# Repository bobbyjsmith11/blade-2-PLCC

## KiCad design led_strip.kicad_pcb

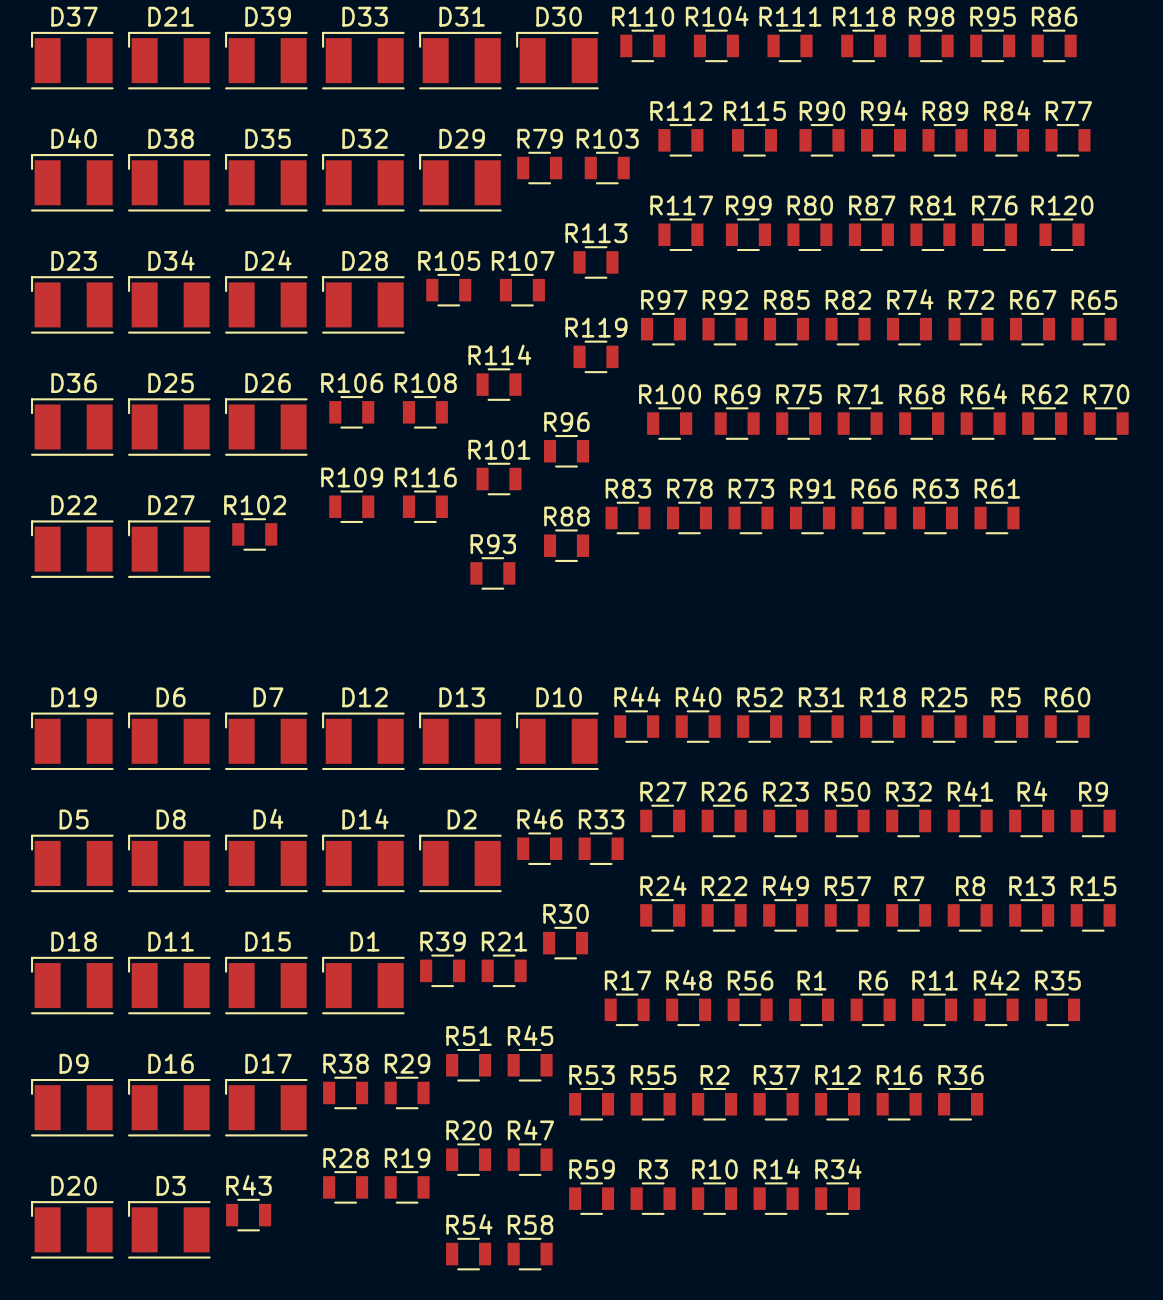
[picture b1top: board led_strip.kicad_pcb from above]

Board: 2 copper layers, 160 parts (0 on the bottom side), 82 nets, no tracks yet.

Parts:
D1, D2, D3, D4, D5, D6, D7, D8, D9, D10, D11, D12, D13, D14, D15, D16, D17, D18, D19, D20, D21, D22, D23, D24, D25, D26, D27, D28, D29, D30, D31, D32, D33, D34, D35, D36, D37, D38, D39, D40: LED; LED_PLCC-2
R1, R4, R7, R10, R13, R16, R19, R22, R25, R28, R31, R34, R37, R40, R43, R46, R49, R52, R55, R58, R61, R64, R67, R70, R73, R76, R79, R82, R85, R88, R91, R94, R97, R100, R103, R106, R109, R112, R115, R118: 287; R_0805
R2, R3, R5, R6, R8, R9, R11, R12, R14, R15, R17, R18, R20, R21, R23, R24, R26, R27, R29, R30, R32, R33, R35, R36, R38, R39, R41, R42, R44, R45, R47, R48, R50, R51, R53, R54, R56, R57, R59, R60, R62, R63, R65, R66, R68, R69, R71, R72, R74, R75, R77, R78, R80, R81, R83, R84, R86, R87, R89, R90, R92, R93, R95, R96, R98, R99, R101, R102, R104, R105, R107, R108, R110, R111, R113, R114, R116, R117, R119, R120: 0; R_0805

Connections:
/Block1/IN: D1.2, R1.2
/Block2/IN: D21.2, R60.1, R61.2
GND: R2.2, R5.2, R8.2, R11.2, R14.2, R17.2, R20.2, R23.2, R26.2, R29.2, R32.2, R35.2, R38.2, R41.2, R44.2, R47.2, R50.2, R53.2, R56.2, R59.2, R62.2, R65.2, R68.2, R71.2, R74.2, R77.2, R80.2, R83.2, R86.2, R89.2, R92.2, R95.2, R98.2, R101.2, R104.2, R107.2, R110.2, R113.2, R116.2, R119.2
unnamed: D1.1, R2.1, R3.2
unnamed: D2.1, R5.1, R6.2
unnamed: D2.2, R3.1, R4.2
unnamed: D3.1, R8.1, R9.2
unnamed: D3.2, R6.1, R7.2
unnamed: D4.1, R11.1, R12.2
unnamed: D4.2, R9.1, R10.2
unnamed: D5.1, R14.1, R15.2
unnamed: D5.2, R12.1, R13.2
unnamed: D6.1, R17.1, R18.2
unnamed: D6.2, R15.1, R16.2
unnamed: D7.1, R20.1, R21.2
unnamed: D7.2, R18.1, R19.2
unnamed: D8.1, R23.1, R24.2
unnamed: D8.2, R21.1, R22.2
unnamed: D9.1, R26.1, R27.2
unnamed: D9.2, R24.1, R25.2
unnamed: D10.1, R29.1, R30.2
unnamed: D10.2, R27.1, R28.2
unnamed: D11.1, R32.1, R33.2
unnamed: D11.2, R30.1, R31.2
unnamed: D12.1, R35.1, R36.2
unnamed: D12.2, R33.1, R34.2
unnamed: D13.1, R38.1, R39.2
unnamed: D13.2, R36.1, R37.2
unnamed: D14.1, R41.1, R42.2
unnamed: D14.2, R39.1, R40.2
unnamed: D15.1, R44.1, R45.2
unnamed: D15.2, R42.1, R43.2
unnamed: D16.1, R47.1, R48.2
unnamed: D16.2, R45.1, R46.2
unnamed: D17.1, R50.1, R51.2
unnamed: D17.2, R48.1, R49.2
unnamed: D18.1, R53.1, R54.2
unnamed: D18.2, R51.1, R52.2
unnamed: D19.1, R56.1, R57.2
unnamed: D19.2, R54.1, R55.2
unnamed: D20.1, R59.1, R60.2
unnamed: D20.2, R57.1, R58.2
unnamed: D21.1, R62.1, R63.2
unnamed: D22.1, R65.1, R66.2
unnamed: D22.2, R63.1, R64.2
unnamed: D23.1, R68.1, R69.2
unnamed: D23.2, R66.1, R67.2
unnamed: D24.1, R71.1, R72.2
unnamed: D24.2, R69.1, R70.2
unnamed: D25.1, R74.1, R75.2
unnamed: D25.2, R72.1, R73.2
unnamed: D26.1, R77.1, R78.2
unnamed: D26.2, R75.1, R76.2
unnamed: D27.1, R80.1, R81.2
unnamed: D27.2, R78.1, R79.2
unnamed: D28.1, R83.1, R84.2
unnamed: D28.2, R81.1, R82.2
unnamed: D29.1, R86.1, R87.2
unnamed: D29.2, R84.1, R85.2
unnamed: D30.1, R89.1, R90.2
unnamed: D30.2, R87.1, R88.2
unnamed: D31.1, R92.1, R93.2
unnamed: D31.2, R90.1, R91.2
unnamed: D32.1, R95.1, R96.2
unnamed: D32.2, R93.1, R94.2
unnamed: D33.1, R98.1, R99.2
unnamed: D33.2, R96.1, R97.2
unnamed: D34.1, R101.1, R102.2
unnamed: D34.2, R99.1, R100.2
unnamed: D35.1, R104.1, R105.2
unnamed: D35.2, R102.1, R103.2
unnamed: D36.1, R107.1, R108.2
unnamed: D36.2, R105.1, R106.2
unnamed: D37.1, R110.1, R111.2
unnamed: D37.2, R108.1, R109.2
unnamed: D38.1, R113.1, R114.2
unnamed: D38.2, R111.1, R112.2
unnamed: D39.1, R116.1, R117.2
unnamed: D39.2, R114.1, R115.2
unnamed: D40.1, R119.1, R120.2
unnamed: D40.2, R117.1, R118.2
VDD: R1.1, R4.1, R7.1, R10.1, R13.1, R16.1, R19.1, R22.1, R25.1, R28.1, R31.1, R34.1, R37.1, R40.1, R43.1, R46.1, R49.1, R52.1, R55.1, R58.1, R61.1, R64.1, R67.1, R70.1, R73.1, R76.1, R79.1, R82.1, R85.1, R88.1, R91.1, R94.1, R97.1, R100.1, R103.1, R106.1, R109.1, R112.1, R115.1, R118.1

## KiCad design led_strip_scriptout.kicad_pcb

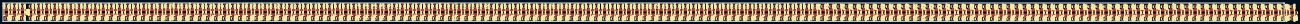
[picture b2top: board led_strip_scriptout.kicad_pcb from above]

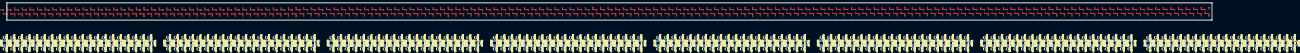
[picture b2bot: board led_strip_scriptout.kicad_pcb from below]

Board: 2 copper layers, 885.2 x 12.7 mm, 1280 parts (640 on the bottom side), 642 nets.

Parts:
D201, D202, D203, D204, D205, D206, D207, D208, D209, D210, D211, D212, D213, D214, D215, D216, D217, D218, D219, D220, D301, D302, D303, D304, D305, D306, D307, D308, D309, D310, D311, D312, D313, D314, D315, D316, D317, D318, D319, D320, D401, D402, D403, D404, D405, D406, D407, D408, D409, D410, D411, D412, D413, D414, D415, D416, D417, D418, D419, D420, D501, D502, D503, D504, D505, D506, D507, D508, D509, D510, D511, D512, D513, D514, D515, D516, D517, D518, D519, D520, D601, D602, D603, D604, D605, D606, D607, D608, D609, D610, D611, D612, D613, D614, D615, D616, D617, D618, D619, D620, D701, D702, D703, D704, D705, D706, D707, D708, D709, D710, D711, D712, D713, D714, D715, D716, D717, D718, D719, D720, D801, D802, D803, D804, D805, D806, D807, D808, D809, D810, D811, D812, D813, D814, D815, D816, D817, D818, D819, D820, D901, D902, D903, D904, D905, D906, D907, D908, D909, D910, D911, D912, D913, D914, D915, D916, D917, D918, D919, D920, D1001, D1002, D1003, D1004, D1005, D1006, D1007, D1008, D1009, D1010, D1011, D1012, D1013, D1014, D1015, D1016, D1017, D1018, D1019, D1020, D1101, D1102, D1103, D1104, D1105, D1106, D1107, D1108, D1109, D1110, D1111, D1112, D1113, D1114, D1115, D1116, D1117, D1118, D1119, D1120, D1201, D1202, D1203, D1204, D1205, D1206, D1207, D1208, D1209, D1210, D1211, D1212, D1213, D1214, D1215, D1216, D1217, D1218, D1219, D1220, D1301, D1302, D1303, D1304, D1305, D1306, D1307, D1308, D1309, D1310, D1311, D1312, D1313, D1314, D1315, D1316, D1317, D1318, D1319, D1320, D1401, D1402, D1403, D1404, D1405, D1406, D1407, D1408, D1409, D1410, D1411, D1412, D1413, D1414, D1415, D1416, D1417, D1418, D1419, D1420, D1501, D1502, D1503, D1504, D1505, D1506, D1507, D1508, D1509, D1510, D1511, D1512, D1513, D1514, D1515, D1516, D1517, D1518, D1519, D1520, D1601, D1602, D1603, D1604, D1605, D1606, D1607, D1608, D1609, D1610, D1611, D1612, D1613, D1614, D1615, D1616, D1617, D1618, D1619, D1620, D1701, D1702, D1703, D1704, D1705, D1706, D1707, D1708, D1709, D1710, D1711, D1712, D1713, D1714, D1715, D1716, D1717, D1718, D1719, D1720: LED; LED_PLCC-2
R201, R204, R207, R210, R213, R216, R219, R222, R225, R228, R231, R234, R237, R240, R243, R246, R249, R252, R255, R258, R301, R304, R307, R310, R313, R316, R319, R322, R325, R328, R331, R334, R337, R340, R343, R346, R349, R352, R355, R358, R401, R404, R407, R410, R413, R416, R419, R422, R425, R428, R431, R434, R437, R440, R443, R446, R449, R452, R455, R458, R501, R504, R507, R510, R513, R516, R519, R522, R525, R528, R531, R534, R537, R540, R543, R546, R549, R552, R555, R558, R601, R604, R607, R610, R613, R616, R619, R622, R625, R628, R631, R634, R637, R640, R643, R646, R649, R652, R655, R658, R701, R704, R707, R710, R713, R716, R719, R722, R725, R728, R731, R734, R737, R740, R743, R746, R749, R752, R755, R758, R801, R804, R807, R810, R813, R816, R819, R822, R825, R828, R831, R834, R837, R840, R843, R846, R849, R852, R855, R858, R901, R904, R907, R910, R913, R916, R919, R922, R925, R928, R931, R934, R937, R940, R943, R946, R949, R952, R955, R958, R1001, R1004, R1007, R1010, R1013, R1016, R1019, R1022, R1025, R1028, R1031, R1034, R1037, R1040, R1043, R1046, R1049, R1052, R1055, R1058, R1101, R1104, R1107, R1110, R1113, R1116, R1119, R1122, R1125, R1128, R1131, R1134, R1137, R1140, R1143, R1146, R1149, R1152, R1155, R1158, R1201, R1204, R1207, R1210, R1213, R1216, R1219, R1222, R1225, R1228, R1231, R1234, R1237, R1240, R1243, R1246, R1249, R1252, R1255, R1258, R1301, R1304, R1307, R1310, R1313, R1316, R1319, R1322, R1325, R1328, R1331, R1334, R1337, R1340, R1343, R1346, R1349, R1352, R1355, R1358, R1401, R1404, R1407, R1410, R1413, R1416, R1419, R1422, R1425, R1428, R1431, R1434, R1437, R1440, R1443, R1446, R1449, R1452, R1455, R1458, R1501, R1504, R1507, R1510, R1513, R1516, R1519, R1522, R1525, R1528, R1531, R1534, R1537, R1540, R1543, R1546, R1549, R1552, R1555, R1558, R1601, R1604, R1607, R1610, R1613, R1616, R1619, R1622, R1625, R1628, R1631, R1634, R1637, R1640, R1643, R1646, R1649, R1652, R1655, R1658, R1701, R1704, R1707, R1710, R1713, R1716, R1719, R1722, R1725, R1728, R1731, R1734, R1737, R1740, R1743, R1746, R1749, R1752, R1755, R1758: 287; R_0805
R202, R203, R205, R206, R208, R209, R211, R212, R214, R215, R217, R218, R220, R221, R223, R224, R226, R227, R229, R230, R232, R233, R235, R236, R238, R239, R241, R242, R244, R245, R247, R248, R250, R251, R253, R254, R256, R257, R259, R260, R302, R303, R305, R306, R308, R309, R311, R312, R314, R315, R317, R318, R320, R321, R323, R324, R326, R327, R329, R330, R332, R333, R335, R336, R338, R339, R341, R342, R344, R345, R347, R348, R350, R351, R353, R354, R356, R357, R359, R360, R402, R403, R405, R406, R408, R409, R411, R412, R414, R415, R417, R418, R420, R421, R423, R424, R426, R427, R429, R430, R432, R433, R435, R436, R438, R439, R441, R442, R444, R445, R447, R448, R450, R451, R453, R454, R456, R457, R459, R460, R502, R503, R505, R506, R508, R509, R511, R512, R514, R515, R517, R518, R520, R521, R523, R524, R526, R527, R529, R530, R532, R533, R535, R536, R538, R539, R541, R542, R544, R545, R547, R548, R550, R551, R553, R554, R556, R557, R559, R560, R602, R603, R605, R606, R608, R609, R611, R612, R614, R615, R617, R618, R620, R621, R623, R624, R626, R627, R629, R630, R632, R633, R635, R636, R638, R639, R641, R642, R644, R645, R647, R648, R650, R651, R653, R654, R656, R657, R659, R660, R702, R703, R705, R706, R708, R709, R711, R712, R714, R715, R717, R718, R720, R721, R723, R724, R726, R727, R729, R730, R732, R733, R735, R736, R738, R739, R741, R742, R744, R745, R747, R748, R750, R751, R753, R754, R756, R757, R759, R760, R802, R803, R805, R806, R808, R809, R811, R812, R814, R815, R817, R818, R820, R821, R823, R824, R826, R827, R829, R830, R832, R833, R835, R836, R838, R839, R841, R842, R844, R845, R847, R848, R850, R851, R853, R854, R856, R857, R859, R860, R902, R903, R905, R906, R908, R909, R911, R912, R914, R915, R917, R918, R920, R921, R923, R924, R926, R927, R929, R930, R932, R933, R935, R936, R938, R939, R941, R942, R944, R945, R947, R948, R950, R951, R953, R954, R956, R957, R959, R960, R1002, R1003, R1005, R1006, R1008, R1009, R1011, R1012, R1014, R1015, R1017, R1018, R1020, R1021, R1023, R1024, R1026, R1027, R1029, R1030, R1032, R1033, R1035, R1036, R1038, R1039, R1041, R1042, R1044, R1045, R1047, R1048, R1050, R1051, R1053, R1054, R1056, R1057, R1059, R1060, R1102, R1103, R1105, R1106, R1108, R1109, R1111, R1112, R1114, R1115, R1117, R1118, R1120, R1121, R1123, R1124, R1126, R1127, R1129, R1130, R1132, R1133, R1135, R1136, R1138, R1139, R1141, R1142, R1144, R1145, R1147, R1148, R1150, R1151, R1153, R1154, R1156, R1157, R1159, R1160, R1202, R1203, R1205, R1206, R1208, R1209, R1211, R1212, R1214, R1215, R1217, R1218, R1220, R1221, R1223, R1224, R1226, R1227, R1229, R1230, R1232, R1233, R1235, R1236, R1238, R1239, R1241, R1242, R1244, R1245, R1247, R1248, R1250, R1251, R1253, R1254, R1256, R1257, R1259, R1260, R1302, R1303, R1305, R1306, R1308, R1309, R1311, R1312, R1314, R1315, R1317, R1318, R1320, R1321, R1323, R1324, R1326, R1327, R1329, R1330, R1332, R1333, R1335, R1336, R1338, R1339, R1341, R1342, R1344, R1345, R1347, R1348, R1350, R1351, R1353, R1354, R1356, R1357, R1359, R1360, R1402, R1403, R1405, R1406, R1408, R1409, R1411, R1412, R1414, R1415, R1417, R1418, R1420, R1421, R1423, R1424, R1426, R1427, R1429, R1430, R1432, R1433, R1435, R1436, R1438, R1439, R1441, R1442, R1444, R1445, R1447, R1448, R1450, R1451, R1453, R1454, R1456, R1457, R1459, R1460, R1502, R1503, R1505, R1506, R1508, R1509, R1511, R1512, R1514, R1515, R1517, R1518, R1520, R1521, R1523, R1524, R1526, R1527, R1529, R1530, R1532, R1533, R1535, R1536, R1538, R1539, R1541, R1542, R1544, R1545, R1547, R1548, R1550, R1551, R1553, R1554, R1556, R1557, R1559, R1560, R1602, R1603, R1605, R1606, R1608, R1609, R1611, R1612, R1614, R1615, R1617, R1618, R1620, R1621, R1623, R1624, R1626, R1627, R1629, R1630, R1632, R1633, R1635, R1636, R1638, R1639, R1641, R1642, R1644, R1645, R1647, R1648, R1650, R1651, R1653, R1654, R1656, R1657, R1659, R1660, R1702, R1703, R1705, R1706, R1708, R1709, R1711, R1712, R1714, R1715, R1717, R1718, R1720, R1721, R1723, R1724, R1726, R1727, R1729, R1730, R1732, R1733, R1735, R1736, R1738, R1739, R1741, R1742, R1744, R1745, R1747, R1748, R1750, R1751, R1753, R1754, R1756, R1757, R1759, R1760: 0; R_0805

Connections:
/Block1/IN: D201.2, R201.2
/Block2/IN: D301.2, R260.1, R301.2
/Block3/IN: D401.2, R360.1, R401.2
/Block4/IN: D501.2, R460.1, R501.2
/Block5/IN: D601.2, R560.1, R601.2
/Block6/IN: D701.2, R660.1, R701.2
/Block7/IN: D801.2, R760.1, R801.2
/Block8/IN: D901.2, R860.1, R901.2
/Block9/IN: D1001.2, R1001.2
/Block10/IN: D1101.2, R1060.1, R1101.2
/Block11/IN: D1201.2, R1160.1, R1201.2
/Block12/IN: D1301.2, R1260.1, R1301.2
/Block13/IN: D1401.2, R1360.1, R1401.2
/Block14/IN: D1501.2, R1460.1, R1501.2
/Block15/IN: D1601.2, R1560.1, R1601.2
/Block16/IN: D1701.2, R1660.1, R1701.2
GND: R202.2, R205.2, R208.2, R211.2, R214.2, R217.2, R220.2, R223.2, R226.2, R229.2, R232.2, R235.2, R238.2, R241.2, R244.2, R247.2, R250.2, R253.2, R256.2, R259.2, R302.2, R305.2, R308.2, R311.2, R314.2, R317.2, R320.2, R323.2, R326.2, R329.2, R332.2, R335.2, R338.2, R341.2, R344.2, R347.2, R350.2, R353.2, R356.2, R359.2, R402.2, R405.2, R408.2, R411.2, R414.2, R417.2, R420.2, R423.2, R426.2, R429.2, R432.2, R435.2, R438.2, R441.2, R444.2, R447.2, R450.2, R453.2, R456.2, R459.2, R502.2, R505.2, R508.2, R511.2, R514.2, R517.2, R520.2, R523.2, R526.2, R529.2, R532.2, R535.2, R538.2, R541.2, R544.2, R547.2, R550.2, R553.2, R556.2, R559.2, R602.2, R605.2, R608.2, R611.2, R614.2, R617.2, R620.2, R623.2, R626.2, R629.2, R632.2, R635.2, R638.2, R641.2, R644.2, R647.2, R650.2, R653.2, R656.2, R659.2, R702.2, R705.2, R708.2, R711.2, R714.2, R717.2, R720.2, R723.2, R726.2, R729.2, R732.2, R735.2, R738.2, R741.2, R744.2, R747.2, R750.2, R753.2, R756.2, R759.2, R802.2, R805.2, R808.2, R811.2, R814.2, R817.2, R820.2, R823.2, R826.2, R829.2, R832.2, R835.2, R838.2, R841.2, R844.2, R847.2, R850.2, R853.2, R856.2, R859.2, R902.2, R905.2, R908.2, R911.2, R914.2, R917.2, R920.2, R923.2, R926.2, R929.2, R932.2, R935.2, R938.2, R941.2, R944.2, R947.2, R950.2, R953.2, R956.2, R959.2, R1002.2, R1005.2, R1008.2, R1011.2, R1014.2, R1017.2, R1020.2, R1023.2, R1026.2, R1029.2, R1032.2, R1035.2, R1038.2, R1041.2, R1044.2, R1047.2, R1050.2, R1053.2, R1056.2, R1059.2, R1102.2, R1105.2, R1108.2, R1111.2, R1114.2, R1117.2, R1120.2, R1123.2, R1126.2, R1129.2, R1132.2, R1135.2, R1138.2, R1141.2, R1144.2, R1147.2, R1150.2, R1153.2, R1156.2, R1159.2, R1202.2, R1205.2, R1208.2, R1211.2, R1214.2, R1217.2, R1220.2, R1223.2, R1226.2, R1229.2, R1232.2, R1235.2, R1238.2, R1241.2, R1244.2, R1247.2, R1250.2, R1253.2, R1256.2, R1259.2, R1302.2, R1305.2, R1308.2, R1311.2, R1314.2, R1317.2, R1320.2, R1323.2, R1326.2, R1329.2, R1332.2, R1335.2, R1338.2, R1341.2, R1344.2, R1347.2, R1350.2, R1353.2, R1356.2, R1359.2, R1402.2, R1405.2, R1408.2, R1411.2, R1414.2, R1417.2, R1420.2, R1423.2, R1426.2, R1429.2, R1432.2, R1435.2, R1438.2, R1441.2, R1444.2, R1447.2, R1450.2, R1453.2, R1456.2, R1459.2, R1502.2, R1505.2, R1508.2, R1511.2, R1514.2, R1517.2, R1520.2, R1523.2, R1526.2, R1529.2, R1532.2, R1535.2, R1538.2, R1541.2, R1544.2, R1547.2, R1550.2, R1553.2, R1556.2, R1559.2, R1602.2, R1605.2, R1608.2, R1611.2, R1614.2, R1617.2, R1620.2, R1623.2, R1626.2, R1629.2, R1632.2, R1635.2, R1638.2, R1641.2, R1644.2, R1647.2, R1650.2, R1653.2, R1656.2, R1659.2, R1702.2, R1705.2, R1708.2, R1711.2, R1714.2, R1717.2, R1720.2, R1723.2, R1726.2, R1729.2, R1732.2, R1735.2, R1738.2, R1741.2, R1744.2, R1747.2, R1750.2, R1753.2, R1756.2, R1759.2
unnamed: D201.1, R202.1, R203.2
unnamed: D202.1, R205.1, R206.2
unnamed: D202.2, R203.1, R204.2
unnamed: D203.1, R208.1, R209.2
unnamed: D203.2, R206.1, R207.2
unnamed: D204.1, R211.1, R212.2
unnamed: D204.2, R209.1, R210.2
unnamed: D205.1, R214.1, R215.2
unnamed: D205.2, R212.1, R213.2
unnamed: D206.1, R217.1, R218.2
unnamed: D206.2, R215.1, R216.2
unnamed: D207.1, R220.1, R221.2
unnamed: D207.2, R218.1, R219.2
unnamed: D208.1, R223.1, R224.2
unnamed: D208.2, R221.1, R222.2
unnamed: D209.1, R226.1, R227.2
unnamed: D209.2, R224.1, R225.2
unnamed: D210.1, R229.1, R230.2
unnamed: D210.2, R227.1, R228.2
unnamed: D211.1, R232.1, R233.2
unnamed: D211.2, R230.1, R231.2
unnamed: D212.1, R235.1, R236.2
unnamed: D212.2, R233.1, R234.2
unnamed: D213.1, R238.1, R239.2
unnamed: D213.2, R236.1, R237.2
unnamed: D214.1, R241.1, R242.2
unnamed: D214.2, R239.1, R240.2
unnamed: D215.1, R244.1, R245.2
unnamed: D215.2, R242.1, R243.2
unnamed: D216.1, R247.1, R248.2
unnamed: D216.2, R245.1, R246.2
unnamed: D217.1, R250.1, R251.2
unnamed: D217.2, R248.1, R249.2
unnamed: D218.1, R253.1, R254.2
unnamed: D218.2, R251.1, R252.2
unnamed: D219.1, R256.1, R257.2
unnamed: D219.2, R254.1, R255.2
unnamed: D220.1, R259.1, R260.2
unnamed: D220.2, R257.1, R258.2
unnamed: D301.1, R302.1, R303.2
unnamed: D302.1, R305.1, R306.2
unnamed: D302.2, R303.1, R304.2
unnamed: D303.1, R308.1, R309.2
unnamed: D303.2, R306.1, R307.2
unnamed: D304.1, R311.1, R312.2
unnamed: D304.2, R309.1, R310.2
unnamed: D305.1, R314.1, R315.2
unnamed: D305.2, R312.1, R313.2
unnamed: D306.1, R317.1, R318.2
unnamed: D306.2, R315.1, R316.2
unnamed: D307.1, R320.1, R321.2
unnamed: D307.2, R318.1, R319.2
unnamed: D308.1, R323.1, R324.2
unnamed: D308.2, R321.1, R322.2
unnamed: D309.1, R326.1, R327.2
unnamed: D309.2, R324.1, R325.2
unnamed: D310.1, R329.1, R330.2
unnamed: D310.2, R327.1, R328.2
unnamed: D311.1, R332.1, R333.2
unnamed: D311.2, R330.1, R331.2
unnamed: D312.1, R335.1, R336.2
unnamed: D312.2, R333.1, R334.2
unnamed: D313.1, R338.1, R339.2
unnamed: D313.2, R336.1, R337.2
unnamed: D314.1, R341.1, R342.2
unnamed: D314.2, R339.1, R340.2
unnamed: D315.1, R344.1, R345.2
unnamed: D315.2, R342.1, R343.2
unnamed: D316.1, R347.1, R348.2
unnamed: D316.2, R345.1, R346.2
unnamed: D317.1, R350.1, R351.2
unnamed: D317.2, R348.1, R349.2
unnamed: D318.1, R353.1, R354.2
unnamed: D318.2, R351.1, R352.2
unnamed: D319.1, R356.1, R357.2
unnamed: D319.2, R354.1, R355.2
unnamed: D320.1, R359.1, R360.2
unnamed: D320.2, R357.1, R358.2
unnamed: D401.1, R402.1, R403.2
unnamed: D402.1, R405.1, R406.2
unnamed: D402.2, R403.1, R404.2
unnamed: D403.1, R408.1, R409.2
unnamed: D403.2, R406.1, R407.2
unnamed: D404.1, R411.1, R412.2
unnamed: D404.2, R409.1, R410.2
unnamed: D405.1, R414.1, R415.2
unnamed: D405.2, R412.1, R413.2
unnamed: D406.1, R417.1, R418.2
unnamed: D406.2, R415.1, R416.2
unnamed: D407.1, R420.1, R421.2
unnamed: D407.2, R418.1, R419.2
unnamed: D408.1, R423.1, R424.2
unnamed: D408.2, R421.1, R422.2
unnamed: D409.1, R426.1, R427.2
unnamed: D409.2, R424.1, R425.2
unnamed: D410.1, R429.1, R430.2
unnamed: D410.2, R427.1, R428.2
unnamed: D411.1, R432.1, R433.2
unnamed: D411.2, R430.1, R431.2
unnamed: D412.1, R435.1, R436.2
unnamed: D412.2, R433.1, R434.2
unnamed: D413.1, R438.1, R439.2
unnamed: D413.2, R436.1, R437.2
unnamed: D414.1, R441.1, R442.2
unnamed: D414.2, R439.1, R440.2
unnamed: D415.1, R444.1, R445.2
unnamed: D415.2, R442.1, R443.2
unnamed: D416.1, R447.1, R448.2
unnamed: D416.2, R445.1, R446.2
unnamed: D417.1, R450.1, R451.2
unnamed: D417.2, R448.1, R449.2
unnamed: D418.1, R453.1, R454.2
unnamed: D418.2, R451.1, R452.2
unnamed: D419.1, R456.1, R457.2
unnamed: D419.2, R454.1, R455.2
unnamed: D420.1, R459.1, R460.2
unnamed: D420.2, R457.1, R458.2
unnamed: D501.1, R502.1, R503.2
unnamed: D502.1, R505.1, R506.2
unnamed: D502.2, R503.1, R504.2
unnamed: D503.1, R508.1, R509.2
unnamed: D503.2, R506.1, R507.2
unnamed: D504.1, R511.1, R512.2
unnamed: D504.2, R509.1, R510.2
unnamed: D505.1, R514.1, R515.2
unnamed: D505.2, R512.1, R513.2
unnamed: D506.1, R517.1, R518.2
unnamed: D506.2, R515.1, R516.2
unnamed: D507.1, R520.1, R521.2
unnamed: D507.2, R518.1, R519.2
unnamed: D508.1, R523.1, R524.2
unnamed: D508.2, R521.1, R522.2
unnamed: D509.1, R526.1, R527.2
unnamed: D509.2, R524.1, R525.2
unnamed: D510.1, R529.1, R530.2
unnamed: D510.2, R527.1, R528.2
unnamed: D511.1, R532.1, R533.2
unnamed: D511.2, R530.1, R531.2
unnamed: D512.1, R535.1, R536.2
unnamed: D512.2, R533.1, R534.2
unnamed: D513.1, R538.1, R539.2
unnamed: D513.2, R536.1, R537.2
unnamed: D514.1, R541.1, R542.2
unnamed: D514.2, R539.1, R540.2
unnamed: D515.1, R544.1, R545.2
unnamed: D515.2, R542.1, R543.2
unnamed: D516.1, R547.1, R548.2
unnamed: D516.2, R545.1, R546.2
unnamed: D517.1, R550.1, R551.2
unnamed: D517.2, R548.1, R549.2
unnamed: D518.1, R553.1, R554.2
unnamed: D518.2, R551.1, R552.2
unnamed: D519.1, R556.1, R557.2
unnamed: D519.2, R554.1, R555.2
unnamed: D520.1, R559.1, R560.2
unnamed: D520.2, R557.1, R558.2
unnamed: D601.1, R602.1, R603.2
unnamed: D602.1, R605.1, R606.2
unnamed: D602.2, R603.1, R604.2
unnamed: D603.1, R608.1, R609.2
unnamed: D603.2, R606.1, R607.2
unnamed: D604.1, R611.1, R612.2
unnamed: D604.2, R609.1, R610.2
unnamed: D605.1, R614.1, R615.2
unnamed: D605.2, R612.1, R613.2
unnamed: D606.1, R617.1, R618.2
unnamed: D606.2, R615.1, R616.2
unnamed: D607.1, R620.1, R621.2
unnamed: D607.2, R618.1, R619.2
unnamed: D608.1, R623.1, R624.2
unnamed: D608.2, R621.1, R622.2
unnamed: D609.1, R626.1, R627.2
unnamed: D609.2, R624.1, R625.2
unnamed: D610.1, R629.1, R630.2
unnamed: D610.2, R627.1, R628.2
unnamed: D611.1, R632.1, R633.2
unnamed: D611.2, R630.1, R631.2
unnamed: D612.1, R635.1, R636.2
unnamed: D612.2, R633.1, R634.2
unnamed: D613.1, R638.1, R639.2
unnamed: D613.2, R636.1, R637.2
unnamed: D614.1, R641.1, R642.2
unnamed: D614.2, R639.1, R640.2
unnamed: D615.1, R644.1, R645.2
unnamed: D615.2, R642.1, R643.2
unnamed: D616.1, R647.1, R648.2
unnamed: D616.2, R645.1, R646.2
unnamed: D617.1, R650.1, R651.2
unnamed: D617.2, R648.1, R649.2
unnamed: D618.1, R653.1, R654.2
unnamed: D618.2, R651.1, R652.2
unnamed: D619.1, R656.1, R657.2
unnamed: D619.2, R654.1, R655.2
unnamed: D620.1, R659.1, R660.2
unnamed: D620.2, R657.1, R658.2
unnamed: D701.1, R702.1, R703.2
unnamed: D702.1, R705.1, R706.2
unnamed: D702.2, R703.1, R704.2
unnamed: D703.1, R708.1, R709.2
unnamed: D703.2, R706.1, R707.2
unnamed: D704.1, R711.1, R712.2
unnamed: D704.2, R709.1, R710.2
unnamed: D705.1, R714.1, R715.2
unnamed: D705.2, R712.1, R713.2
unnamed: D706.1, R717.1, R718.2
unnamed: D706.2, R715.1, R716.2
unnamed: D707.1, R720.1, R721.2
unnamed: D707.2, R718.1, R719.2
unnamed: D708.1, R723.1, R724.2
unnamed: D708.2, R721.1, R722.2
unnamed: D709.1, R726.1, R727.2
unnamed: D709.2, R724.1, R725.2
unnamed: D710.1, R729.1, R730.2
unnamed: D710.2, R727.1, R728.2
unnamed: D711.1, R732.1, R733.2
unnamed: D711.2, R730.1, R731.2
unnamed: D712.1, R735.1, R736.2
unnamed: D712.2, R733.1, R734.2
unnamed: D713.1, R738.1, R739.2
unnamed: D713.2, R736.1, R737.2
unnamed: D714.1, R741.1, R742.2
unnamed: D714.2, R739.1, R740.2
unnamed: D715.1, R744.1, R745.2
unnamed: D715.2, R742.1, R743.2
unnamed: D716.1, R747.1, R748.2
unnamed: D716.2, R745.1, R746.2
unnamed: D717.1, R750.1, R751.2
unnamed: D717.2, R748.1, R749.2
unnamed: D718.1, R753.1, R754.2
unnamed: D718.2, R751.1, R752.2
unnamed: D719.1, R756.1, R757.2
unnamed: D719.2, R754.1, R755.2
unnamed: D720.1, R759.1, R760.2
unnamed: D720.2, R757.1, R758.2
unnamed: D801.1, R802.1, R803.2
unnamed: D802.1, R805.1, R806.2
unnamed: D802.2, R803.1, R804.2
unnamed: D803.1, R808.1, R809.2
unnamed: D803.2, R806.1, R807.2
unnamed: D804.1, R811.1, R812.2
unnamed: D804.2, R809.1, R810.2
unnamed: D805.1, R814.1, R815.2
unnamed: D805.2, R812.1, R813.2
unnamed: D806.1, R817.1, R818.2
unnamed: D806.2, R815.1, R816.2
unnamed: D807.1, R820.1, R821.2
unnamed: D807.2, R818.1, R819.2
unnamed: D808.1, R823.1, R824.2
unnamed: D808.2, R821.1, R822.2
unnamed: D809.1, R826.1, R827.2
unnamed: D809.2, R824.1, R825.2
unnamed: D810.1, R829.1, R830.2
unnamed: D810.2, R827.1, R828.2
unnamed: D811.1, R832.1, R833.2
unnamed: D811.2, R830.1, R831.2
unnamed: D812.1, R835.1, R836.2
unnamed: D812.2, R833.1, R834.2
unnamed: D813.1, R838.1, R839.2
unnamed: D813.2, R836.1, R837.2
unnamed: D814.1, R841.1, R842.2
unnamed: D814.2, R839.1, R840.2
unnamed: D815.1, R844.1, R845.2
unnamed: D815.2, R842.1, R843.2
unnamed: D816.1, R847.1, R848.2
unnamed: D816.2, R845.1, R846.2
unnamed: D817.1, R850.1, R851.2
unnamed: D817.2, R848.1, R849.2
unnamed: D818.1, R853.1, R854.2
unnamed: D818.2, R851.1, R852.2
unnamed: D819.1, R856.1, R857.2
unnamed: D819.2, R854.1, R855.2
unnamed: D820.1, R859.1, R860.2
unnamed: D820.2, R857.1, R858.2
unnamed: D901.1, R902.1, R903.2
unnamed: D902.1, R905.1, R906.2
unnamed: D902.2, R903.1, R904.2
unnamed: D903.1, R908.1, R909.2
unnamed: D903.2, R906.1, R907.2
unnamed: D904.1, R911.1, R912.2
unnamed: D904.2, R909.1, R910.2
unnamed: D905.1, R914.1, R915.2
unnamed: D905.2, R912.1, R913.2
unnamed: D906.1, R917.1, R918.2
unnamed: D906.2, R915.1, R916.2
unnamed: D907.1, R920.1, R921.2
unnamed: D907.2, R918.1, R919.2
unnamed: D908.1, R923.1, R924.2
unnamed: D908.2, R921.1, R922.2
unnamed: D909.1, R926.1, R927.2
unnamed: D909.2, R924.1, R925.2
unnamed: D910.1, R929.1, R930.2
unnamed: D910.2, R927.1, R928.2
unnamed: D911.1, R932.1, R933.2
unnamed: D911.2, R930.1, R931.2
unnamed: D912.1, R935.1, R936.2
unnamed: D912.2, R933.1, R934.2
unnamed: D913.1, R938.1, R939.2
unnamed: D913.2, R936.1, R937.2
unnamed: D914.1, R941.1, R942.2
unnamed: D914.2, R939.1, R940.2
unnamed: D915.1, R944.1, R945.2
unnamed: D915.2, R942.1, R943.2
unnamed: D916.1, R947.1, R948.2
unnamed: D916.2, R945.1, R946.2
unnamed: D917.1, R950.1, R951.2
unnamed: D917.2, R948.1, R949.2
unnamed: D918.1, R953.1, R954.2
unnamed: D918.2, R951.1, R952.2
unnamed: D919.1, R956.1, R957.2
unnamed: D919.2, R954.1, R955.2
unnamed: D920.1, R959.1, R960.2
unnamed: D920.2, R957.1, R958.2
unnamed: D1001.1, R1002.1, R1003.2
unnamed: D1002.1, R1005.1, R1006.2
unnamed: D1002.2, R1003.1, R1004.2
unnamed: D1003.1, R1008.1, R1009.2
unnamed: D1003.2, R1006.1, R1007.2
unnamed: D1004.1, R1011.1, R1012.2
unnamed: D1004.2, R1009.1, R1010.2
unnamed: D1005.1, R1014.1, R1015.2
unnamed: D1005.2, R1012.1, R1013.2
unnamed: D1006.1, R1017.1, R1018.2
unnamed: D1006.2, R1015.1, R1016.2
unnamed: D1007.1, R1020.1, R1021.2
unnamed: D1007.2, R1018.1, R1019.2
unnamed: D1008.1, R1023.1, R1024.2
unnamed: D1008.2, R1021.1, R1022.2
unnamed: D1009.1, R1026.1, R1027.2
unnamed: D1009.2, R1024.1, R1025.2
unnamed: D1010.1, R1029.1, R1030.2
unnamed: D1010.2, R1027.1, R1028.2
unnamed: D1011.1, R1032.1, R1033.2
unnamed: D1011.2, R1030.1, R1031.2
unnamed: D1012.1, R1035.1, R1036.2
unnamed: D1012.2, R1033.1, R1034.2
unnamed: D1013.1, R1038.1, R1039.2
unnamed: D1013.2, R1036.1, R1037.2
unnamed: D1014.1, R1041.1, R1042.2
unnamed: D1014.2, R1039.1, R1040.2
unnamed: D1015.1, R1044.1, R1045.2
unnamed: D1015.2, R1042.1, R1043.2
unnamed: D1016.1, R1047.1, R1048.2
unnamed: D1016.2, R1045.1, R1046.2
unnamed: D1017.1, R1050.1, R1051.2
unnamed: D1017.2, R1048.1, R1049.2
unnamed: D1018.1, R1053.1, R1054.2
unnamed: D1018.2, R1051.1, R1052.2
unnamed: D1019.1, R1056.1, R1057.2
unnamed: D1019.2, R1054.1, R1055.2
unnamed: D1020.1, R1059.1, R1060.2
unnamed: D1020.2, R1057.1, R1058.2
unnamed: D1101.1, R1102.1, R1103.2
unnamed: D1102.1, R1105.1, R1106.2
unnamed: D1102.2, R1103.1, R1104.2
unnamed: D1103.1, R1108.1, R1109.2
unnamed: D1103.2, R1106.1, R1107.2
unnamed: D1104.1, R1111.1, R1112.2
unnamed: D1104.2, R1109.1, R1110.2
unnamed: D1105.1, R1114.1, R1115.2
unnamed: D1105.2, R1112.1, R1113.2
unnamed: D1106.1, R1117.1, R1118.2
unnamed: D1106.2, R1115.1, R1116.2
unnamed: D1107.1, R1120.1, R1121.2
unnamed: D1107.2, R1118.1, R1119.2
unnamed: D1108.1, R1123.1, R1124.2
unnamed: D1108.2, R1121.1, R1122.2
unnamed: D1109.1, R1126.1, R1127.2
unnamed: D1109.2, R1124.1, R1125.2
unnamed: D1110.1, R1129.1, R1130.2
unnamed: D1110.2, R1127.1, R1128.2
unnamed: D1111.1, R1132.1, R1133.2
unnamed: D1111.2, R1130.1, R1131.2
unnamed: D1112.1, R1135.1, R1136.2
unnamed: D1112.2, R1133.1, R1134.2
unnamed: D1113.1, R1138.1, R1139.2
unnamed: D1113.2, R1136.1, R1137.2
unnamed: D1114.1, R1141.1, R1142.2
unnamed: D1114.2, R1139.1, R1140.2
unnamed: D1115.1, R1144.1, R1145.2
unnamed: D1115.2, R1142.1, R1143.2
unnamed: D1116.1, R1147.1, R1148.2
unnamed: D1116.2, R1145.1, R1146.2
unnamed: D1117.1, R1150.1, R1151.2
unnamed: D1117.2, R1148.1, R1149.2
unnamed: D1118.1, R1153.1, R1154.2
unnamed: D1118.2, R1151.1, R1152.2
unnamed: D1119.1, R1156.1, R1157.2
unnamed: D1119.2, R1154.1, R1155.2
unnamed: D1120.1, R1159.1, R1160.2
unnamed: D1120.2, R1157.1, R1158.2
unnamed: D1201.1, R1202.1, R1203.2
unnamed: D1202.1, R1205.1, R1206.2
unnamed: D1202.2, R1203.1, R1204.2
unnamed: D1203.1, R1208.1, R1209.2
unnamed: D1203.2, R1206.1, R1207.2
unnamed: D1204.1, R1211.1, R1212.2
unnamed: D1204.2, R1209.1, R1210.2
unnamed: D1205.1, R1214.1, R1215.2
unnamed: D1205.2, R1212.1, R1213.2
unnamed: D1206.1, R1217.1, R1218.2
unnamed: D1206.2, R1215.1, R1216.2
unnamed: D1207.1, R1220.1, R1221.2
unnamed: D1207.2, R1218.1, R1219.2
unnamed: D1208.1, R1223.1, R1224.2
unnamed: D1208.2, R1221.1, R1222.2
unnamed: D1209.1, R1226.1, R1227.2
unnamed: D1209.2, R1224.1, R1225.2
unnamed: D1210.1, R1229.1, R1230.2
unnamed: D1210.2, R1227.1, R1228.2
unnamed: D1211.1, R1232.1, R1233.2
unnamed: D1211.2, R1230.1, R1231.2
unnamed: D1212.1, R1235.1, R1236.2
unnamed: D1212.2, R1233.1, R1234.2
unnamed: D1213.1, R1238.1, R1239.2
unnamed: D1213.2, R1236.1, R1237.2
unnamed: D1214.1, R1241.1, R1242.2
unnamed: D1214.2, R1239.1, R1240.2
unnamed: D1215.1, R1244.1, R1245.2
unnamed: D1215.2, R1242.1, R1243.2
unnamed: D1216.1, R1247.1, R1248.2
unnamed: D1216.2, R1245.1, R1246.2
unnamed: D1217.1, R1250.1, R1251.2
unnamed: D1217.2, R1248.1, R1249.2
unnamed: D1218.1, R1253.1, R1254.2
unnamed: D1218.2, R1251.1, R1252.2
unnamed: D1219.1, R1256.1, R1257.2
unnamed: D1219.2, R1254.1, R1255.2
unnamed: D1220.1, R1259.1, R1260.2
unnamed: D1220.2, R1257.1, R1258.2
unnamed: D1301.1, R1302.1, R1303.2
unnamed: D1302.1, R1305.1, R1306.2
unnamed: D1302.2, R1303.1, R1304.2
unnamed: D1303.1, R1308.1, R1309.2
unnamed: D1303.2, R1306.1, R1307.2
unnamed: D1304.1, R1311.1, R1312.2
unnamed: D1304.2, R1309.1, R1310.2
unnamed: D1305.1, R1314.1, R1315.2
unnamed: D1305.2, R1312.1, R1313.2
unnamed: D1306.1, R1317.1, R1318.2
unnamed: D1306.2, R1315.1, R1316.2
unnamed: D1307.1, R1320.1, R1321.2
unnamed: D1307.2, R1318.1, R1319.2
unnamed: D1308.1, R1323.1, R1324.2
unnamed: D1308.2, R1321.1, R1322.2
unnamed: D1309.1, R1326.1, R1327.2
unnamed: D1309.2, R1324.1, R1325.2
unnamed: D1310.1, R1329.1, R1330.2
unnamed: D1310.2, R1327.1, R1328.2
unnamed: D1311.1, R1332.1, R1333.2
unnamed: D1311.2, R1330.1, R1331.2
unnamed: D1312.1, R1335.1, R1336.2
unnamed: D1312.2, R1333.1, R1334.2
unnamed: D1313.1, R1338.1, R1339.2
unnamed: D1313.2, R1336.1, R1337.2
unnamed: D1314.1, R1341.1, R1342.2
unnamed: D1314.2, R1339.1, R1340.2
unnamed: D1315.1, R1344.1, R1345.2
unnamed: D1315.2, R1342.1, R1343.2
unnamed: D1316.1, R1347.1, R1348.2
unnamed: D1316.2, R1345.1, R1346.2
unnamed: D1317.1, R1350.1, R1351.2
unnamed: D1317.2, R1348.1, R1349.2
unnamed: D1318.1, R1353.1, R1354.2
unnamed: D1318.2, R1351.1, R1352.2
unnamed: D1319.1, R1356.1, R1357.2
unnamed: D1319.2, R1354.1, R1355.2
unnamed: D1320.1, R1359.1, R1360.2
unnamed: D1320.2, R1357.1, R1358.2
unnamed: D1401.1, R1402.1, R1403.2
unnamed: D1402.1, R1405.1, R1406.2
unnamed: D1402.2, R1403.1, R1404.2
unnamed: D1403.1, R1408.1, R1409.2
unnamed: D1403.2, R1406.1, R1407.2
unnamed: D1404.1, R1411.1, R1412.2
unnamed: D1404.2, R1409.1, R1410.2
unnamed: D1405.1, R1414.1, R1415.2
unnamed: D1405.2, R1412.1, R1413.2
unnamed: D1406.1, R1417.1, R1418.2
unnamed: D1406.2, R1415.1, R1416.2
unnamed: D1407.1, R1420.1, R1421.2
unnamed: D1407.2, R1418.1, R1419.2
unnamed: D1408.1, R1423.1, R1424.2
unnamed: D1408.2, R1421.1, R1422.2
unnamed: D1409.1, R1426.1, R1427.2
unnamed: D1409.2, R1424.1, R1425.2
unnamed: D1410.1, R1429.1, R1430.2
unnamed: D1410.2, R1427.1, R1428.2
unnamed: D1411.1, R1432.1, R1433.2
unnamed: D1411.2, R1430.1, R1431.2
unnamed: D1412.1, R1435.1, R1436.2
unnamed: D1412.2, R1433.1, R1434.2
unnamed: D1413.1, R1438.1, R1439.2
unnamed: D1413.2, R1436.1, R1437.2
unnamed: D1414.1, R1441.1, R1442.2
unnamed: D1414.2, R1439.1, R1440.2
unnamed: D1415.1, R1444.1, R1445.2
unnamed: D1415.2, R1442.1, R1443.2
unnamed: D1416.1, R1447.1, R1448.2
unnamed: D1416.2, R1445.1, R1446.2
unnamed: D1417.1, R1450.1, R1451.2
unnamed: D1417.2, R1448.1, R1449.2
unnamed: D1418.1, R1453.1, R1454.2
unnamed: D1418.2, R1451.1, R1452.2
unnamed: D1419.1, R1456.1, R1457.2
unnamed: D1419.2, R1454.1, R1455.2
unnamed: D1420.1, R1459.1, R1460.2
unnamed: D1420.2, R1457.1, R1458.2
unnamed: D1501.1, R1502.1, R1503.2
unnamed: D1502.1, R1505.1, R1506.2
unnamed: D1502.2, R1503.1, R1504.2
unnamed: D1503.1, R1508.1, R1509.2
unnamed: D1503.2, R1506.1, R1507.2
unnamed: D1504.1, R1511.1, R1512.2
unnamed: D1504.2, R1509.1, R1510.2
unnamed: D1505.1, R1514.1, R1515.2
unnamed: D1505.2, R1512.1, R1513.2
unnamed: D1506.1, R1517.1, R1518.2
unnamed: D1506.2, R1515.1, R1516.2
unnamed: D1507.1, R1520.1, R1521.2
unnamed: D1507.2, R1518.1, R1519.2
unnamed: D1508.1, R1523.1, R1524.2
unnamed: D1508.2, R1521.1, R1522.2
unnamed: D1509.1, R1526.1, R1527.2
unnamed: D1509.2, R1524.1, R1525.2
unnamed: D1510.1, R1529.1, R1530.2
unnamed: D1510.2, R1527.1, R1528.2
unnamed: D1511.1, R1532.1, R1533.2
unnamed: D1511.2, R1530.1, R1531.2
unnamed: D1512.1, R1535.1, R1536.2
unnamed: D1512.2, R1533.1, R1534.2
unnamed: D1513.1, R1538.1, R1539.2
unnamed: D1513.2, R1536.1, R1537.2
unnamed: D1514.1, R1541.1, R1542.2
unnamed: D1514.2, R1539.1, R1540.2
unnamed: D1515.1, R1544.1, R1545.2
unnamed: D1515.2, R1542.1, R1543.2
unnamed: D1516.1, R1547.1, R1548.2
unnamed: D1516.2, R1545.1, R1546.2
unnamed: D1517.1, R1550.1, R1551.2
unnamed: D1517.2, R1548.1, R1549.2
unnamed: D1518.1, R1553.1, R1554.2
unnamed: D1518.2, R1551.1, R1552.2
unnamed: D1519.1, R1556.1, R1557.2
unnamed: D1519.2, R1554.1, R1555.2
unnamed: D1520.1, R1559.1, R1560.2
unnamed: D1520.2, R1557.1, R1558.2
unnamed: D1601.1, R1602.1, R1603.2
unnamed: D1602.1, R1605.1, R1606.2
unnamed: D1602.2, R1603.1, R1604.2
unnamed: D1603.1, R1608.1, R1609.2
unnamed: D1603.2, R1606.1, R1607.2
unnamed: D1604.1, R1611.1, R1612.2
unnamed: D1604.2, R1609.1, R1610.2
unnamed: D1605.1, R1614.1, R1615.2
unnamed: D1605.2, R1612.1, R1613.2
unnamed: D1606.1, R1617.1, R1618.2
unnamed: D1606.2, R1615.1, R1616.2
unnamed: D1607.1, R1620.1, R1621.2
unnamed: D1607.2, R1618.1, R1619.2
unnamed: D1608.1, R1623.1, R1624.2
unnamed: D1608.2, R1621.1, R1622.2
unnamed: D1609.1, R1626.1, R1627.2
unnamed: D1609.2, R1624.1, R1625.2
unnamed: D1610.1, R1629.1, R1630.2
unnamed: D1610.2, R1627.1, R1628.2
unnamed: D1611.1, R1632.1, R1633.2
unnamed: D1611.2, R1630.1, R1631.2
unnamed: D1612.1, R1635.1, R1636.2
unnamed: D1612.2, R1633.1, R1634.2
unnamed: D1613.1, R1638.1, R1639.2
unnamed: D1613.2, R1636.1, R1637.2
unnamed: D1614.1, R1641.1, R1642.2
unnamed: D1614.2, R1639.1, R1640.2
unnamed: D1615.1, R1644.1, R1645.2
unnamed: D1615.2, R1642.1, R1643.2
unnamed: D1616.1, R1647.1, R1648.2
unnamed: D1616.2, R1645.1, R1646.2
unnamed: D1617.1, R1650.1, R1651.2
unnamed: D1617.2, R1648.1, R1649.2
unnamed: D1618.1, R1653.1, R1654.2
unnamed: D1618.2, R1651.1, R1652.2
unnamed: D1619.1, R1656.1, R1657.2
unnamed: D1619.2, R1654.1, R1655.2
unnamed: D1620.1, R1659.1, R1660.2
unnamed: D1620.2, R1657.1, R1658.2
unnamed: D1701.1, R1702.1, R1703.2
unnamed: D1702.1, R1705.1, R1706.2
unnamed: D1702.2, R1703.1, R1704.2
unnamed: D1703.1, R1708.1, R1709.2
unnamed: D1703.2, R1706.1, R1707.2
unnamed: D1704.1, R1711.1, R1712.2
unnamed: D1704.2, R1709.1, R1710.2
unnamed: D1705.1, R1714.1, R1715.2
unnamed: D1705.2, R1712.1, R1713.2
unnamed: D1706.1, R1717.1, R1718.2
unnamed: D1706.2, R1715.1, R1716.2
unnamed: D1707.1, R1720.1, R1721.2
unnamed: D1707.2, R1718.1, R1719.2
unnamed: D1708.1, R1723.1, R1724.2
unnamed: D1708.2, R1721.1, R1722.2
unnamed: D1709.1, R1726.1, R1727.2
unnamed: D1709.2, R1724.1, R1725.2
unnamed: D1710.1, R1729.1, R1730.2
unnamed: D1710.2, R1727.1, R1728.2
unnamed: D1711.1, R1732.1, R1733.2
unnamed: D1711.2, R1730.1, R1731.2
unnamed: D1712.1, R1735.1, R1736.2
unnamed: D1712.2, R1733.1, R1734.2
unnamed: D1713.1, R1738.1, R1739.2
unnamed: D1713.2, R1736.1, R1737.2
unnamed: D1714.1, R1741.1, R1742.2
unnamed: D1714.2, R1739.1, R1740.2
unnamed: D1715.1, R1744.1, R1745.2
unnamed: D1715.2, R1742.1, R1743.2
unnamed: D1716.1, R1747.1, R1748.2
unnamed: D1716.2, R1745.1, R1746.2
unnamed: D1717.1, R1750.1, R1751.2
unnamed: D1717.2, R1748.1, R1749.2
unnamed: D1718.1, R1753.1, R1754.2
unnamed: D1718.2, R1751.1, R1752.2
unnamed: D1719.1, R1756.1, R1757.2
unnamed: D1719.2, R1754.1, R1755.2
unnamed: D1720.1, R1759.1, R1760.2
unnamed: D1720.2, R1757.1, R1758.2
VDD: R201.1, R204.1, R207.1, R210.1, R213.1, R216.1, R219.1, R222.1, R225.1, R228.1, R231.1, R234.1, R237.1, R240.1, R243.1, R246.1, R249.1, R252.1, R255.1, R258.1, R301.1, R304.1, R307.1, R310.1, R313.1, R316.1, R319.1, R322.1, R325.1, R328.1, R331.1, R334.1, R337.1, R340.1, R343.1, R346.1, R349.1, R352.1, R355.1, R358.1, R401.1, R404.1, R407.1, R410.1, R413.1, R416.1, R419.1, R422.1, R425.1, R428.1, R431.1, R434.1, R437.1, R440.1, R443.1, R446.1, R449.1, R452.1, R455.1, R458.1, R501.1, R504.1, R507.1, R510.1, R513.1, R516.1, R519.1, R522.1, R525.1, R528.1, R531.1, R534.1, R537.1, R540.1, R543.1, R546.1, R549.1, R552.1, R555.1, R558.1, R601.1, R604.1, R607.1, R610.1, R613.1, R616.1, R619.1, R622.1, R625.1, R628.1, R631.1, R634.1, R637.1, R640.1, R643.1, R646.1, R649.1, R652.1, R655.1, R658.1, R701.1, R704.1, R707.1, R710.1, R713.1, R716.1, R719.1, R722.1, R725.1, R728.1, R731.1, R734.1, R737.1, R740.1, R743.1, R746.1, R749.1, R752.1, R755.1, R758.1, R801.1, R804.1, R807.1, R810.1, R813.1, R816.1, R819.1, R822.1, R825.1, R828.1, R831.1, R834.1, R837.1, R840.1, R843.1, R846.1, R849.1, R852.1, R855.1, R858.1, R901.1, R904.1, R907.1, R910.1, R913.1, R916.1, R919.1, R922.1, R925.1, R928.1, R931.1, R934.1, R937.1, R940.1, R943.1, R946.1, R949.1, R952.1, R955.1, R958.1, R1001.1, R1004.1, R1007.1, R1010.1, R1013.1, R1016.1, R1019.1, R1022.1, R1025.1, R1028.1, R1031.1, R1034.1, R1037.1, R1040.1, R1043.1, R1046.1, R1049.1, R1052.1, R1055.1, R1058.1, R1101.1, R1104.1, R1107.1, R1110.1, R1113.1, R1116.1, R1119.1, R1122.1, R1125.1, R1128.1, R1131.1, R1134.1, R1137.1, R1140.1, R1143.1, R1146.1, R1149.1, R1152.1, R1155.1, R1158.1, R1201.1, R1204.1, R1207.1, R1210.1, R1213.1, R1216.1, R1219.1, R1222.1, R1225.1, R1228.1, R1231.1, R1234.1, R1237.1, R1240.1, R1243.1, R1246.1, R1249.1, R1252.1, R1255.1, R1258.1, R1301.1, R1304.1, R1307.1, R1310.1, R1313.1, R1316.1, R1319.1, R1322.1, R1325.1, R1328.1, R1331.1, R1334.1, R1337.1, R1340.1, R1343.1, R1346.1, R1349.1, R1352.1, R1355.1, R1358.1, R1401.1, R1404.1, R1407.1, R1410.1, R1413.1, R1416.1, R1419.1, R1422.1, R1425.1, R1428.1, R1431.1, R1434.1, R1437.1, R1440.1, R1443.1, R1446.1, R1449.1, R1452.1, R1455.1, R1458.1, R1501.1, R1504.1, R1507.1, R1510.1, R1513.1, R1516.1, R1519.1, R1522.1, R1525.1, R1528.1, R1531.1, R1534.1, R1537.1, R1540.1, R1543.1, R1546.1, R1549.1, R1552.1, R1555.1, R1558.1, R1601.1, R1604.1, R1607.1, R1610.1, R1613.1, R1616.1, R1619.1, R1622.1, R1625.1, R1628.1, R1631.1, R1634.1, R1637.1, R1640.1, R1643.1, R1646.1, R1649.1, R1652.1, R1655.1, R1658.1, R1701.1, R1704.1, R1707.1, R1710.1, R1713.1, R1716.1, R1719.1, R1722.1, R1725.1, R1728.1, R1731.1, R1734.1, R1737.1, R1740.1, R1743.1, R1746.1, R1749.1, R1752.1, R1755.1, R1758.1
